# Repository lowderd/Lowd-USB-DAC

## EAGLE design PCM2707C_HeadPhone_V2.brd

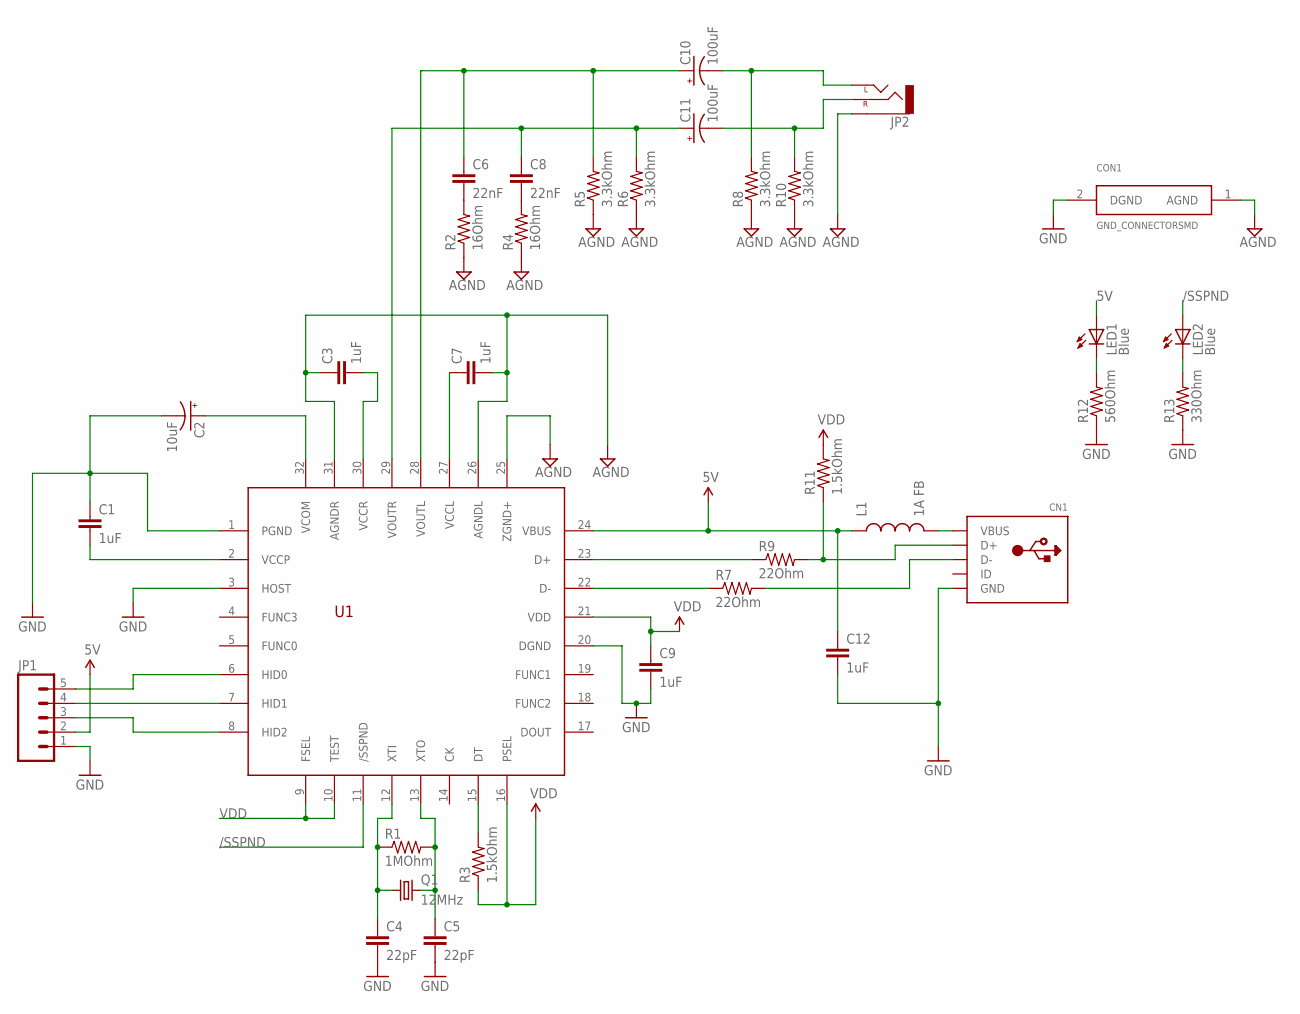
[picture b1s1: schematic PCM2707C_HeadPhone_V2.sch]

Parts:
C1, C3, C7, C9, C12: 1uF; 0805
C2: 10uF; PANASONIC_C
C4, C5: 22pF; 0805
C6, C8: 22nF; 1210
C10, C11: 100uF; PANASONIC_D
CN1: USBMINIB; USB-MINIB
CON1: GND_CONNECTORSMD; GND_CONNECTOR
JP1: M05LOCK; 1X05_LOCK
JP2: AUDIO-JACKPTH; AUDIO-JACK
L1: 1A FB; 0805
LED1, LED2: Blue; LED-0603
Q1: 12MHz; HC49U-V
R1: 1MOhm; 0805
R2, R4: 16Ohm; 0805
R3, R11: 1.5kOhm; 0805
R5, R6, R8, R10: 3.3kOhm; 0805
R7, R9: 22Ohm; 0805
R12: 560Ohm; 0805
R13: 330Ohm; 0805
U1: PCM2707C_TQFP32"; 32TQFP_PCM2707C

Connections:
5V: C12.1, JP1.2, L1.1, LED1.A, U1.24 (VBUS)
/SSPND: LED2.A, U1.11 (/SSPND)
AGND: C3.1, C7.2, CON1.1 (AGND), JP2.SLEEVE, R2.1, R4.1, R5.1, R6.1, R8.1, R10.1, U1.25 (ZGND+), U1.26 (AGNDL), U1.31 (AGNDR)
GND: C1.1, C2.-, C4.2, C5.2, C9.2, C12.2, CN1.GND, CON1.2 (DGND), JP1.1, R12.1, R13.1, U1.1 (PGND), U1.3 (HOST), U1.20 (DGND)
unnamed: JP1.5, U1.6 (HID0)
unnamed: C1.2, U1.2 (VCCP)
unnamed: JP1.4, U1.7 (HID1)
unnamed: C2.+, U1.32 (VCOM)
unnamed: JP1.3, U1.8 (HID2)
unnamed: CN1.VBUS, L1.2
unnamed: C4.1, Q1.1, R1.1, U1.12 (XTI)
unnamed: C5.1, Q1.2, R1.2, U1.13 (XTO)
unnamed: R9.1, U1.23 (D+)
unnamed: R7.1, U1.22 (D-)
unnamed: CN1.D+, R9.2, R11.1
unnamed: CN1.D-, R7.2
unnamed: C3.2, U1.30 (VCCR)
unnamed: LED1.C, R12.2
unnamed: R3.2, U1.15 (DT)
unnamed: C7.1, U1.27 (VCCL)
unnamed: C8.2, R4.2
unnamed: C6.2, R2.2
unnamed: C11.-, JP2.RING (RIGHT), R10.2
unnamed: C10.-, JP2.TIP (LEFT), R8.2
unnamed: C8.1, C11.+, R6.2, U1.29 (VOUTR)
unnamed: LED2.C, R13.2
unnamed: C6.1, C10.+, R5.2, U1.28 (VOUTL)
VDD: C9.1, R3.1, R11.2, U1.9 (FSEL), U1.10 (TEST), U1.16 (PSEL), U1.21 (VDD)

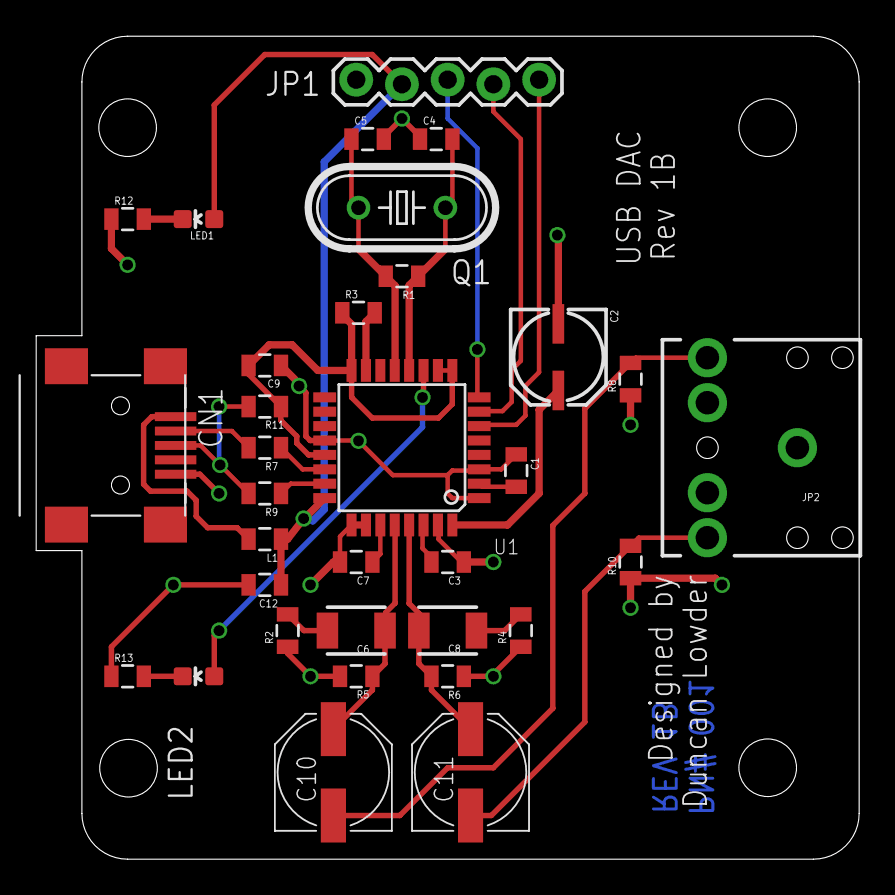
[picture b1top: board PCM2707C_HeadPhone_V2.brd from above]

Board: 2 copper layers, 45.7 x 45.7 mm, 34 parts (1 on the bottom side), 28 nets.

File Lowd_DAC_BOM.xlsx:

Bill Of Materials - Lowd USB DAC
Number of Devices: |  | 1
Item # | Designator | Name | Description | Manufacturer | Mfg. Part # | Distributor | Quantity
1 | C1, C3, C7, C9, C12 | 1uF Cap | CAP CER 1UF 16V Y5V 0805 | Samsung Electro-Mechanics America Inc. | CL21F105ZOCNNNC | Digikey | 5
2 | C2 | 10uF Cap | CAP ALUM 10UF 25V 20% SMD | Panasonic Electronic Components | EEE-HA1E100R | Digikey | 1
3 | C4, C5 | 22pF Cap | CAP CER 22PF 50V 5% NP0 0805 | Kernet | C0805C220J5GACTU | Digikey | 2
4 | C6, C8 | 22nF Audio Cap | CAP FILM 0.022UF 50VDC 1210 | Panasonic Electronic Components | ECH-U1H223GX5 | Digikey | 2
5 | C10, C11 | 100uF Audio Cap | CAP ALUM 100UF 25V 20% SMD | Nichicon | UUQ1E101MCL1GS | Digikey | 2
6 | CN1 | Mini USB Conn | CONN MINI USB RCPT RA TYPE B SMD | FCI | 10033526-N3212LF | Digikey | 1
7 | JP2 | Audio Conn | CONN JACK STEREO R/A 3PIN 3.5MM | CUI Inc | SJ1-3523N | Digikey | 1
8 | L1 | Ferrite Bead | FERRITE BEAD 47 OHM 0805 | Taiyo Yuden | BK2125HS470-T | Digikey | 1
9 | LED1, LED2 | Indicator LEDs | LED 468NM BLUE CLEAR 0603 SMD | Lite-On Inc | LTST-C191TBKT | Digikey | 2
10 | Q1 | 12MHz Crystal | CRYSTAL 12MHZ 18PF THRU | TXC Corporation | 9B-12.000MAAJ-B | Digikey | 1
11 | R1 | 1MOhm Resistor | RES SMD 1M OHM 5% 1/8W 0805 | Stackpole Electronics Inc | RMCF0805JT1M00 | Digikey | 1
12 | R2, R4 | 16 Ohm Audio Resistor | RES SMD 16 OHM 1% 1/8W 0805 | Yageo | RC0805FR-0716RL | Digikey | 2
13 | R3, R11 | 1.5KOhm Resistor | RES SMD 1.5K OHM 1% 1/8W 0805 | Yageo | RC0805FR-071K5L | Digikey | 2
14 | R5, R6, R8, R10 | 3.3KOhm Audio Resistor | RES SMD 3.3K OHM 1% 1/8W 0805 | Rohm | MCR10ERTF3301 | Digikey | 4
15 | R7, R9 | 22 Ohm Resistor | RES SMD 22 OHM 1% 1/8W 0805 | Yageo | RC0805FR-0722RL | Digikey | 2
16 | R12 | 560 Ohm Resistor | RES SMD 560 OHM 5% 1/8W 0805 | Stackpole Electronics Inc | RMCF0805JT560R | Digikey | 1
17 | R13 | 330 Ohm Resistor | RES SMD 330 OHM 5% 1/8W 0805 | Stackpole Electronics Inc | RMCF0805JT330R | Digikey | 1
18 | U1 | PCM2707 USB DAC | IC DAC 16BIT STEREO W/USB 32TQFP | Texas Instruments | PCM2707PJTR | Digikey | 1
Mechanical Parts
19 | TOP | Case Top | CASE TOP | Ponoko | N/A | N/A | 1
20 | BOT | Case Bottom | CASE BOTTOM | Ponoko | N/A | N/A | 1
21 | SIDE | Case Sides | CASE SIDE | Ponoko | N/A | N/A | 6
22 | NUT1 | Nut for Case Screw | M3 18-8 STAINLESS STEEL ACORN NUT | McMaster-Carr | 94000A330 | McMaster-Carr | 4
23 | WASH1 | PCB Spacer | M3 NYLON FLAT WASHER | McMaster-Carr | 95610A530 | McMaster-Carr | 8
24 | SCREW1 | Case Screw | M3 16MM STAINLESS STEEL HEX CAP SCREW | McMaster-Carr | 90666A107 | McMaster-Carr | 4
25 | SCREW2 | PCB Screw | M3 10MM STAINLESS STEEL HEX CAP SCREW | McMaster-Carr | 90666A105 | McMaster-Carr | 4
26 | NUT2 | Nut for PCB screw | M3 STAINLESS STEEL HEX NUT | McMaster-Carr | 91828A211 | McMaster-Carr | 4
27 | PCB1 | PCB for USB DAC | PCB | OshPark | N/A | N/A | 1

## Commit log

2015-03-12 3d platic model
    A new design for the board's case, because I didn't like the original
    design.
2015-03-12 readme modify for the screw to show

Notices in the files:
parts and their libraries:
SparkFun-Passives: Licensing: Creative Commons ShareAlike 4.0 International - https://creativecommons.org/licenses/by-sa/4.0
